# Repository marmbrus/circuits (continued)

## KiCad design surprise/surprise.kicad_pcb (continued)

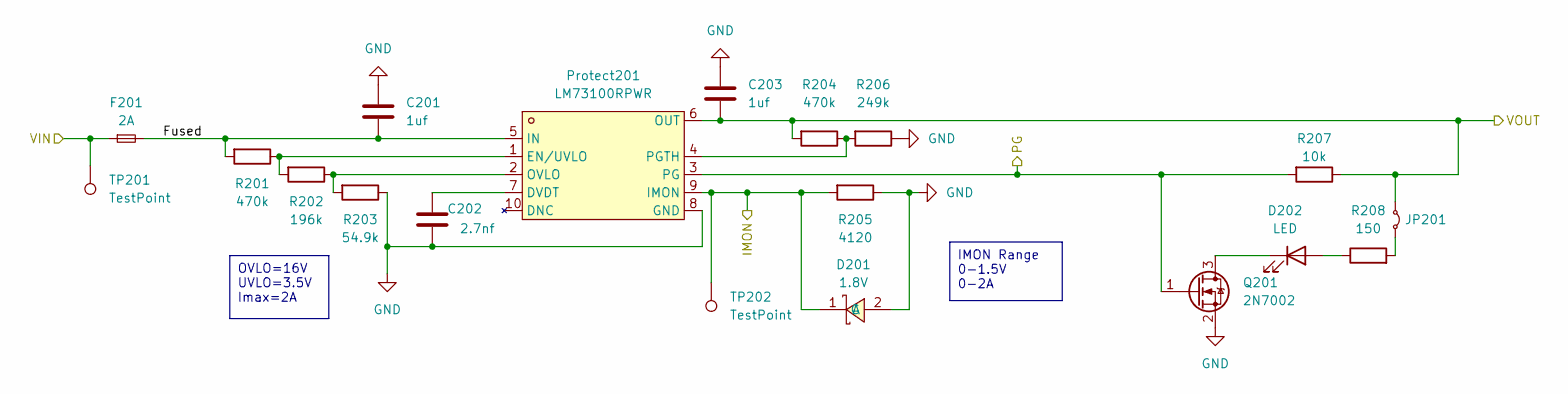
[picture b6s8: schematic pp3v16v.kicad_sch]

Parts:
C201, C203: 1uf; C_0603_1608Metric
C202: 2.7nf; C_0603_1608Metric
D201: 1.8V; SOD-123_L2.7-W1.6-LS3.7-RD; LCSC Part C150464
D202: LED; LED_0603_1608Metric; LCSC Part C2286
F201: 2A; Fuse_1206_3216Metric; LCSC Part C2924939
JP201: JP1; SolderJumper-2_P1.3mm_Bridged_RoundedPad1.0x1.5mm
Protect201: LM73100RPWR; VQFN-10_L2.0-W2.0-P0.45-TL; LCSC Part C3210761
Q201: 2N7002; SOT-23
R201, R204: 470k; R_0603_1608Metric
R202: 196k; R_0603_1608Metric
R203: 54.9k; R_0603_1608Metric
R205: 4120; R_0603_1608Metric
R206: 249k; R_0603_1608Metric
R207: 10k; R_0603_1608Metric
R208: 150; R_0603_1608Metric
TP201, TP202: TestPoint; Pin_D1.0mm_L10.0mm

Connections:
/PowerProtect/Fused: C201.2, F201.2, Protect201.5 (IN), R201.2
/PowerProtect/IMON: D201.1 (C), Protect201.9 (IMON), R205.2, TP202.1
/PowerProtect/PG: Protect201.3 (PG), Q201.1 (G), R207.2; also elsewhere on the board
/PowerProtect/VIN: F201.1, TP201.1; also elsewhere on the board
/PowerProtect/VOUT: C203.2, JP201.1 (A), Protect201.6 (OUT), R204.2, R207.1; also elsewhere on the board
GND: C201.1, C202.2, C203.1, D201.2 (A), Protect201.8 (GND), Q201.2 (S), R203.1, R205.1, R206.1; also elsewhere on the board
unnamed: D202.2 (A), R208.1
unnamed: D202.1 (K), Q201.3 (D)
unnamed: JP201.2 (B), R208.2
unnamed: C202.1, Protect201.7 (DVDT)
unnamed: Protect201.1 (EN/UVLO), R201.1, R202.2
unnamed: Protect201.2 (OVLO), R202.1, R203.2
unnamed: Protect201.4 (PGTH), R204.1, R206.2

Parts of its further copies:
C501, C503: 1uf; C_0603_1608Metric
C502: 2.7nf; C_0603_1608Metric
D501: 1.8V; SOD-123_L2.7-W1.6-LS3.7-RD; LCSC Part C150464
D502: LED; LED_0603_1608Metric; LCSC Part C2286
F501: 2A; Fuse_1206_3216Metric; LCSC Part C2924939
JP501: JP1; SolderJumper-2_P1.3mm_Bridged_RoundedPad1.0x1.5mm
Protect501: LM73100RPWR; VQFN-10_L2.0-W2.0-P0.45-TL; LCSC Part C3210761
Q501: 2N7002; SOT-23
R501, R504: 470k; R_0603_1608Metric
R502: 196k; R_0603_1608Metric
R503: 54.9k; R_0603_1608Metric
R505: 4120; R_0603_1608Metric
R506: 249k; R_0603_1608Metric
R507: 10k; R_0603_1608Metric
R508: 150; R_0603_1608Metric
TP501, TP502: TestPoint; Pin_D1.0mm_L10.0mm

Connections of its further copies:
/PowerProtect1/Fused: C501.2, F501.2, Protect501.5 (IN), R501.2
/PowerProtect1/IMON: D501.1 (C), Protect501.9 (IMON), R505.2, TP502.1
/PowerProtect1/PG: Protect501.3 (PG), Q501.1 (G), R507.2; also elsewhere on the board
/PowerProtect1/VIN: F501.1, TP501.1; also elsewhere on the board
/PowerProtect1/VOUT: C503.2, JP501.1 (A), Protect501.6 (OUT), R504.2, R507.1; also elsewhere on the board
GND: C501.1, C502.2, C503.1, D501.2 (A), Protect501.8 (GND), Q501.2 (S), R503.1, R505.1, R506.1; also elsewhere on the board
unnamed: D502.2 (A), R508.1
unnamed: D502.1 (K), Q501.3 (D)
unnamed: JP501.2 (B), R508.2
unnamed: C502.1, Protect501.7 (DVDT)
unnamed: Protect501.1 (EN/UVLO), R501.1, R502.2
unnamed: Protect501.2 (OVLO), R502.1, R503.2
unnamed: Protect501.4 (PGTH), R504.1, R506.2

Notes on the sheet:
IMON Range 0-1.5V 0-2A
OVLO=16V UVLO=3.5V Imax=2A

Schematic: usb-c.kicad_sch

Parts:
C701: 100nf; C_0603_1608Metric
R701: 0; R_0603_1608Metric; not fitted
R702, R703: 5.1k; R_0603_1608Metric
U701: USBLC6-2SC6; SOT-23-6
USBC701: TYPE-C-31-M-12; USB-C_SMD-TYPE-C-31-M-12; LCSC Part C165948

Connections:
/PowerProtect1/VIN: C701.1, U701.5 (VBUS), USBC701.A4 (VBUS), USBC701.A9 (VBUS), USBC701.B4 (VBUS), USBC701.B9 (VBUS); also elsewhere on the board
/esp32/d+: U701.6 (I/O1); also elsewhere on the board
/esp32/d-: U701.4 (I/O2); also elsewhere on the board
GND: C701.2, R701.2, R702.2, R703.2, U701.2 (GND), USBC701.A1 (GND), USBC701.A12 (GND), USBC701.B1 (GND), USBC701.B12 (GND); also elsewhere on the board
unnamed: R701.1, USBC701.0 (SH), USBC701.1 (SH), USBC701.2 (SH), USBC701.3 (SH)
unnamed: R702.1, USBC701.A5 (CC1)
unnamed: R703.1, USBC701.B5 (CC2)
unnamed: U701.3 (I/O2), USBC701.A7 (DN1), USBC701.B7 (DN2)
unnamed: U701.1 (I/O1), USBC701.A6 (DP1), USBC701.B6 (DP2)

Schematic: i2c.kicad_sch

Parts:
CN1301: BM04B-SRSS-TB(LF)(SN); CONN-SMD_BM04B-SRSS-TB; LCSC Part C160390
Q1301, Q1302: BSS138; SOT-23
R1301, R1302: 10k; R_0603_1608Metric

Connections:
3v3: Q1301.1 (G), Q1302.1 (G); also elsewhere on the board
+5V: CN1301.2, R1301.1, R1302.1; also elsewhere on the board
/battery/SCL: Q1301.2 (S); also elsewhere on the board
/battery/SDA: Q1302.2 (S); also elsewhere on the board
GND: CN1301.1; also elsewhere on the board
unnamed: CN1301.4, Q1301.3 (D), R1302.2
unnamed: CN1301.3, Q1302.3 (D), R1301.2

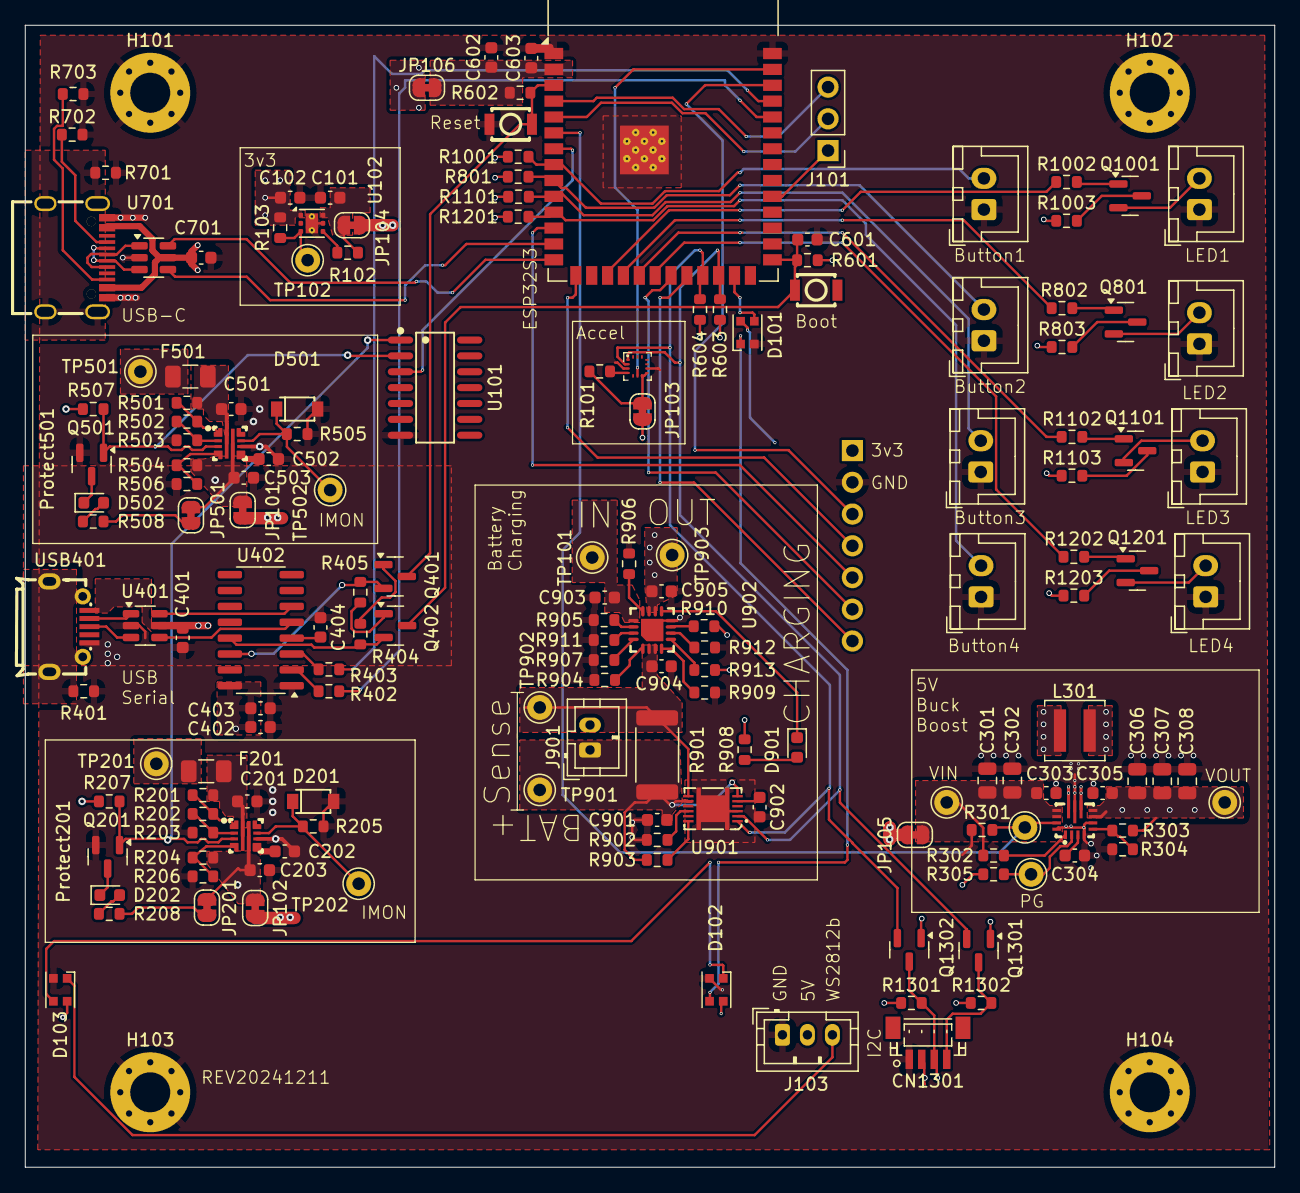
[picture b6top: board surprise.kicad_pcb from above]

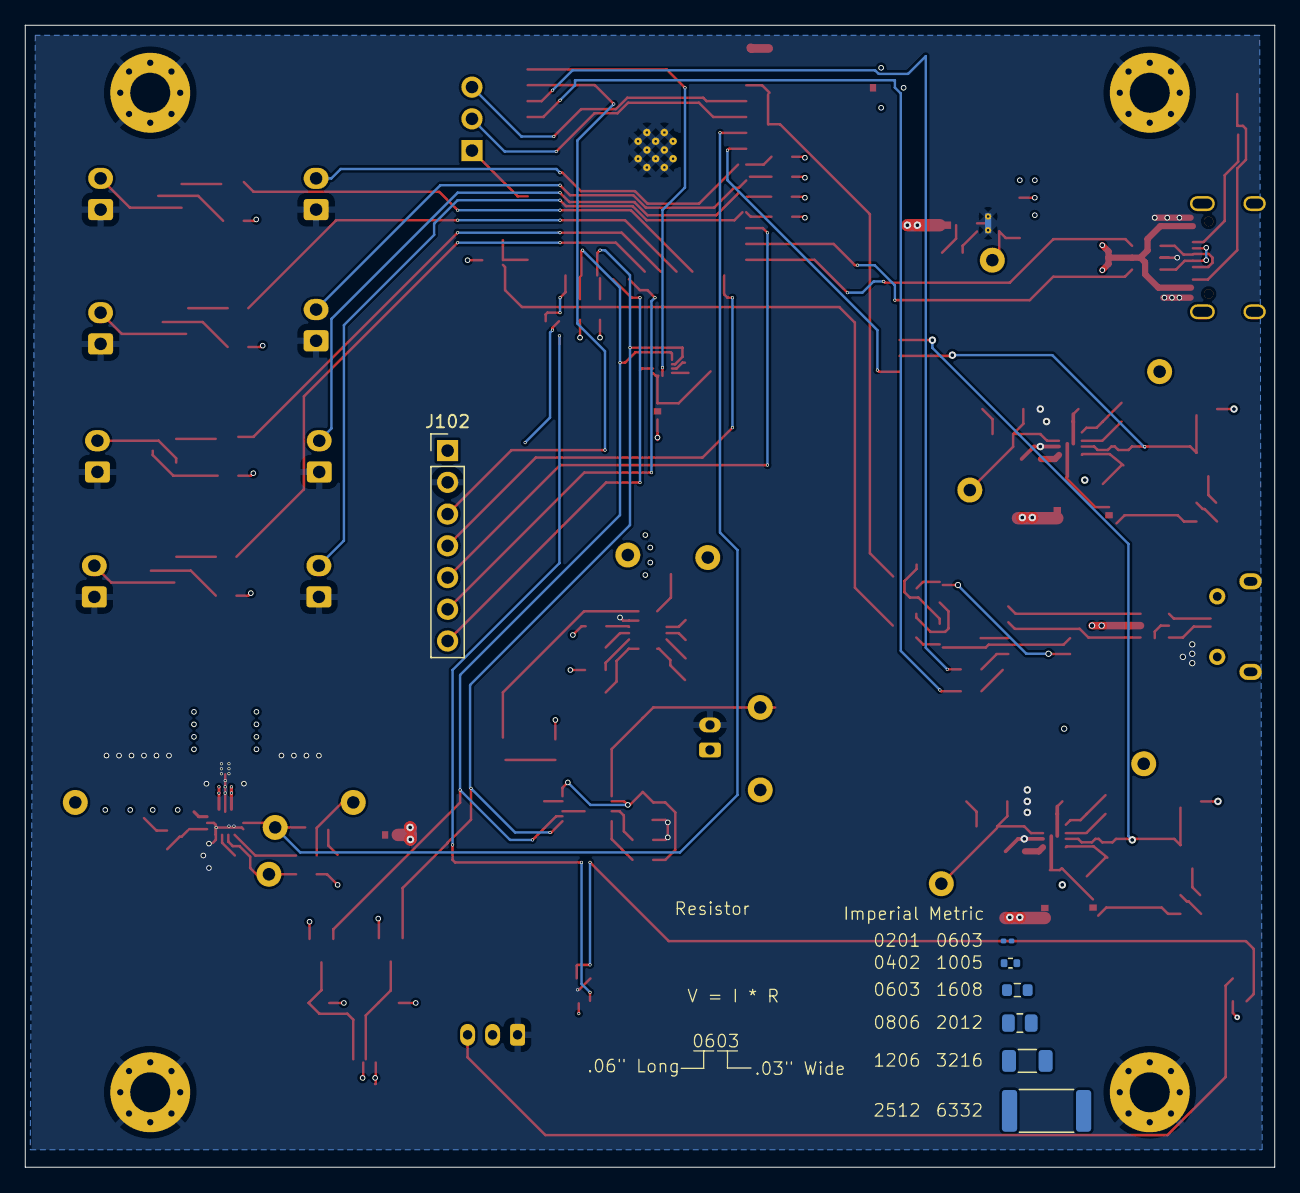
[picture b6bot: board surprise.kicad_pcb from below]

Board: 4 copper layers, 100.0 x 91.4 mm, 173 parts (7 on the bottom side), 120 nets.

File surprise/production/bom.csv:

Designator,Footprint,Quantity,Value,LCSC Part #
"C101, C102, C303, C305, C402",0603,5,10uF,
"C201, C203, C501, C503, C601, C901, C903",0603,7,1uf,
"C202, C502",0603,2,2.7nf,
"C301, C302",0805,2,10uf,
"C304, C401, C403, C404, C603, C701",0603,6,100nf,
"C306, C307, C308",0805,3,22uf,
C602,0603,1,22uF,
C902,0603,1,.47uF,
"C904, C905",0603,2,4.7uF,
CN1301,CONN-SMD_BM04B-SRSS-TB,1,BM04B-SRSS-TB(LF)(SN),C160390
"D101, D102, D103",LED_WS2812B-2020_PLCC4_2.0x2.0mm,3,WS2812B-2020,
"D201, D501",SOD-123_L2.7-W1.6-LS3.7-RD,2,1.8V,C150464
"D202, D502, D901",0603,3,LED,C2286
"F201, F501",1206,2,2A,C2924939
"J1001, J1002, J1101, J1102, J1201, J1202, J801, J802",JST_XH_B2B-XH-A_1x02_P2.50mm_Vertical,8,Conn_01x02,C158012
J101,PinHeader_1x03_P2.54mm_Vertical,1,HB-PH3-25413PB2GOP,
J102,PinHeader_1x07_P2.54mm_Vertical,1,PM254V-11-07-H85,
J103,JST_PH_B3B-PH-K_1x03_P2.00mm_Vertical,1,Conn_01x03,C131339
J901,JST_PH_B2B-PH-K_1x02_P2.00mm_Vertical,1,B2B-PH-K-S(LF)(SN),
L301,L_Coilcraft_XAL4020-XXX,1,1uH,C4555951
"Protect201, Protect501",VQFN-10_L2.0-W2.0-P0.45-TL,2,LM73100RPWR,C3210761
"Q1001, Q1101, Q1201, Q801",SOT-23,4,AO3400A,
"Q1301, Q1302",SOT-23,2,BSS138,
"Q201, Q501",SOT-23,2,2N7002,
"Q401, Q402",SOT-23,2,MMBT3904,
"R1001, R101, R102, R103, R1101, R1201, R1301, R1302, R207, R301, R302, R305, R507, R601, R602, R801, R902, R903, R904, R909, R910, R911, R912, R913",0603,24,10k,
"R1002, R1102, R1202, R802",0603,4,100,
"R1003, R1103, R1203, R803",0603,4,330,
R1401,0201,1,R,
R1402,0402,1,R,
R1403,0603,1,R,
R1404,0805,1,R,
R1405,1206,1,R,
R1406,2512,1,R,
"R201, R204, R501, R504",0603,4,470k,
"R202, R502",0603,2,196k,
"R203, R503",0603,2,54.9k,
"R205, R505",0603,2,4120,
"R206, R506",0603,2,249k,
"R208, R508",0603,2,150,
R303,0603,1,680k,
R304,0603,1,130k,
"R402, R403",0603,2,470,
"R404, R405",0603,2,12k,
"R603, R604",0603,2,4.7k,
"R702, R703",0603,2,5.1k,
R901,2512,1,10mOhm,
R905,0603,1,18k,
"R906, R907",0603,2,2k,
R908,0603,1,1.5k,
"SW602, SW603",KEY-SMD_B3U-1000PM,2,KEY-SMD_B3U-1000PM,C231329
U101,SOIC-14_L8.7-W3.9-P1.27-LS6.0-BL,1,SN74LVC32ADR,C7852
U102,WSON-6-1EP_2x2mm_P0.65mm_EP1x1.6mm_ThermalVias,1,LP5912-3.3DRV,
U103,LGA-14_L2.0-W2.0-P0.35-BL,1,LIS2DHTR,C155670
U301,VQFN-HR-15_L3.0-W2.5-P0.50-BL_TPS63070RNMR,1,TPS63070RNMR,C109322
"U401, U701",SOT-23-6,2,USBLC6-2SC6,
U402,SOIC-16_3.9x9.9mm_P1.27mm,1,CH340C,
U601,ESP32-S3-WROOM-1,1,ESP32-S3-WROOM-1,
U901,SON-12_L4.0-W2.5-P0.40-BL-EP,1,BQ27441DRZR-G1A,C473397
U902,QFN-16_L3.0-W3.0-P0.50-TL-EP1.7,1,BQ24075RGTR,C15464
USB401,MICRO-USB-SMD_MICROXNJ,1,MICROXNJ,C404969
USBC701,USB-C_SMD-TYPE-C-31-M-12,1,TYPE-C-31-M-12,C165948
